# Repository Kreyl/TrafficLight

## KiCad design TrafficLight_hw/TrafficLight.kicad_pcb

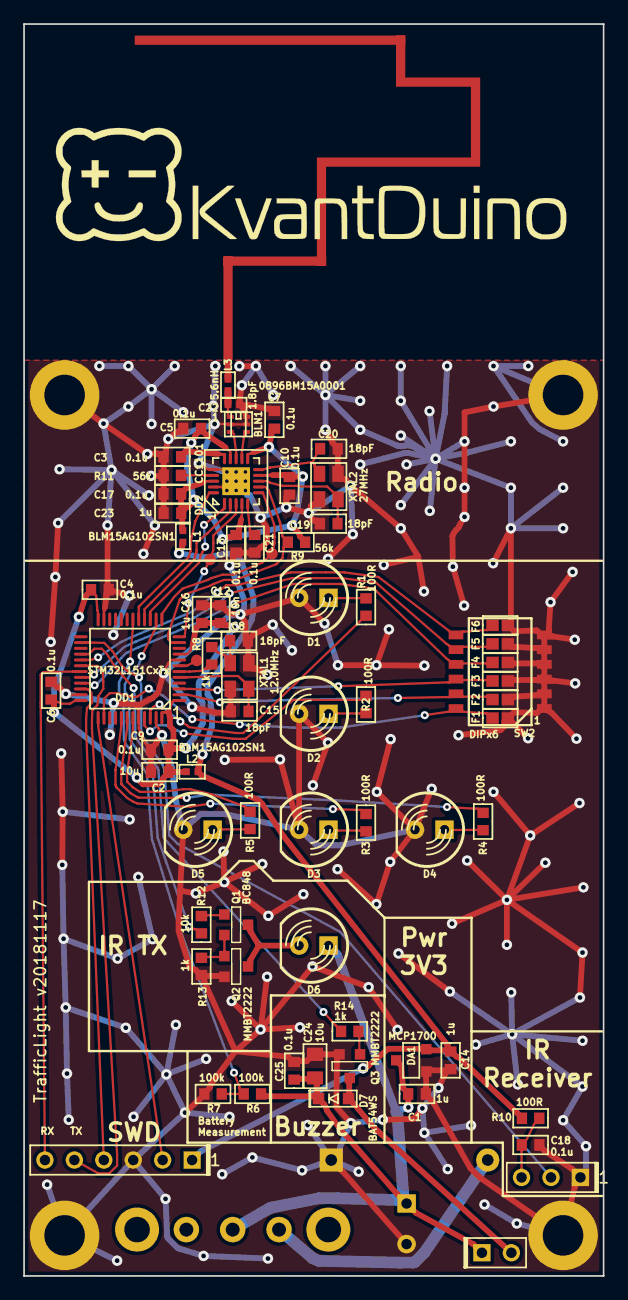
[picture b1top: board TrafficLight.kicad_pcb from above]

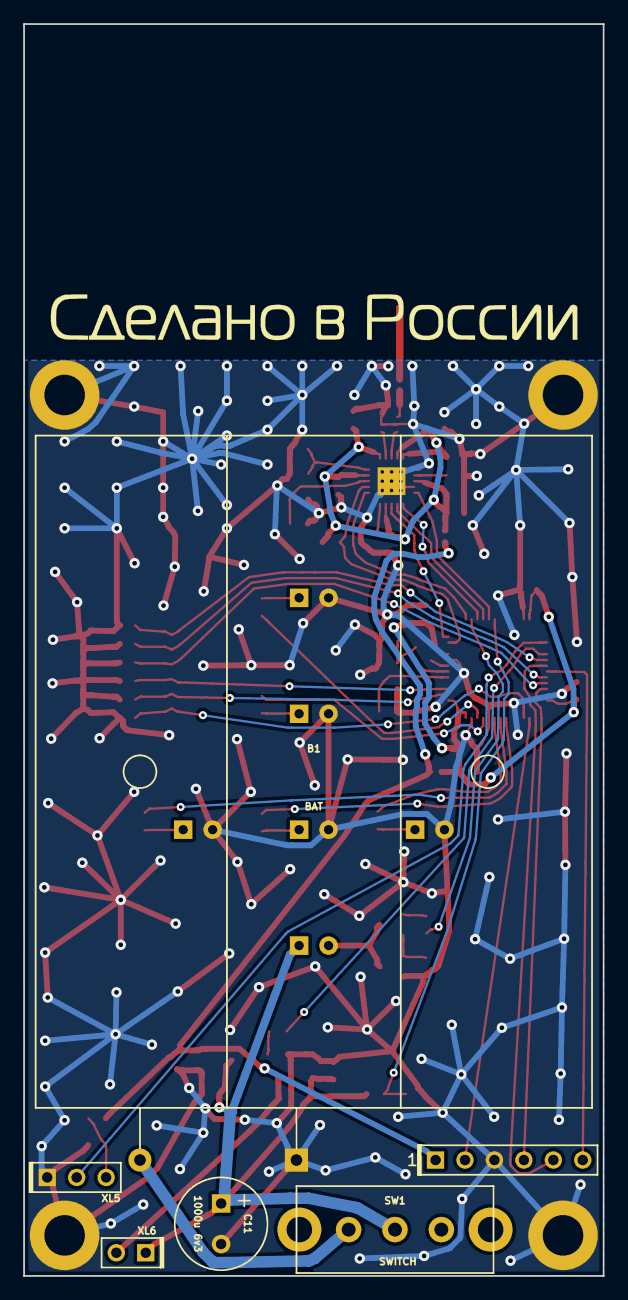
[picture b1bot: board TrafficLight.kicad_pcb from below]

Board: 2 copper layers, 50.0 x 108.0 mm, 80 parts (7 on the bottom side), 54 nets.

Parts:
ANT1: ANT_PCB_MONO; ANT_868_MEANDER_4HOR_35mm
B1: BAT; BAT_HOLDER_3xAA
BLN1: 0896BM15A0001; BALUN_JOHANSON868
C1, C14, C16, C23: 1u; CAP_0603
C2: 10u; CAP_0603
C3, C4, C5, C6, C7, C9, C10, C13, C17, C18, C21, C25: 0.1u; CAP_0603
C8, C15, C19, C20: 18pF; CAP_0603
C11: 1000u 6v3; CAP_08xxR
C12: 10n; CAP_0603
C22: 1.8pF; CAP_0402
C24: 10u; CAP_0805
D1, D2, D3, D4, D5, D6: LED; LED_Through-Hole-5mm
D7: BAT54WS; SOD323
DA1: MCP1700; SOT23-3A
DD1: STM32L151CxTx; LQFP48
DD2: CC1101; QFN20
F1, F2, F3, F4, F5, F6: Fuse0R; RES_0603_FUSE
HOLE1, HOLE2, HOLE3, HOLE4: HOLE_METALLED; Hole3_5_out6mm
L1, L2: BLM15AG102SN1; IND_0402
L3: 5.6nH; IND_0402
Logo1: Logo; KvantduinoLogoText_44d4
Logo3: Logo; MadeInRussia_47d4
Q1: BC848; SOT23-3
Q2, Q3: MMBT2222; SOT23-3
R1, R2, R3, R4, R5, R10: 100R; RES_0603
R6, R7: 100k; RES_0603
R8, R13, R14: 1k; RES_0603
R9, R11: 56k; RES_0603
R12: 10k; RES_0603
SW1: SWITCH; SW_SS9
SW2: DIPx6; DIP_SMD_1D27X6
TP1, TP2, TP3: TESTPOINT; TESTPOINT_1MM
XL1: CONN_6; PLS-6
XL5: CONN_3; PLS-3
XL6: CONN_2; PLS-2
XTAL1: 12.0MHz; 03225C4
XTAL2: 27MHz; 03225C4

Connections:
+3.3V: C14.1, DA1.2, L1.2, L2.2, R10.2, XL1.1
+BATT: C1.1, C11.1, C24.1, C25.1, D6.A, D7.C, DA1.3, R6.1, SW1.2, XL6.1
/ANT1: BLN1.1, C22.1, L3.2
/ANT2: ANT1.1, L3.1
/BAT_IN: B1.A, SW1.1
/BAT_MEAS: DD1.18, R6.2, R7.1
/Buzzer: DD1.28, R14.1
/CC_CS: DD1.11, DD2.7, R9.1
/CC_GDO0: DD1.13, DD2.6, TP2.1
/CC_GDO2: DD1.12, DD2.3, TP3.1
/CC_MISO: DD1.16, DD2.2
/CC_MOSI: DD1.17, DD2.20
/CC_SCK: DD1.15, DD2.1
/DS1: DD1.38, F1.1, SW2.12
/DS2: DD1.2, F2.1, SW2.11
/DS3: DD1.3, F3.1, SW2.10
/DS4: DD1.33, F4.1, SW2.9
/DS5: DD1.32, F5.1, SW2.8
/DS6: DD1.29, F6.1, SW2.7
/IR_LED: DD1.14, R12.1
/IR_LED_OUT: D6.C, Q1.3, Q2.3
/IR_RX: DD1.26, XL5.2
/LEFT_LED: DD1.43, R5.1
/RED_LED: DD1.46, R1.1
/RF1: BLN1.4, DD2.12
/RF2: BLN1.3, DD2.13
/RIGHT_LED: DD1.42, R4.1
/STRAIGHT_LED: DD1.41, R3.1
/SWCLK: DD1.37, XL1.2
/SWDIO: DD1.34, XL1.4
/UART_RX: DD1.31, XL1.6
/UART_TX: DD1.30, XL1.5
/VibroOut: D7.A, Q3.3, XL6.2
/YELLOW_LED: DD1.45, R2.1
GND: B1.C, BLN1.2, BLN1.5, BLN1.6, C1.2, C2.2, C3.2, C4.2, C5.2, C6.2, C7.2, C8.2, C9.2, C10.2, C11.2, C12.2, C13.2, C14.2, C15.2, C16.2, C17.2, C18.1, C19.2, C20.2, C21.2, C22.2, C23.2, C24.2, C25.2, D1.C, D2.C, D3.C, D4.C, D5.C, DA1.1, DD1.8, DD1.23, DD1.35, DD1.44, DD1.47, DD2.16, DD2.19, DD2.PAD, F1.2, F2.2, F3.2, F4.2, F5.2, F6.2, HOLE1.H, HOLE2.H, HOLE3.H, HOLE4.H, Q2.2, Q3.2, R7.2, R11.2, R13.1, SW2.1, SW2.2, SW2.3, SW2.4, SW2.5, SW2.6, XL1.3, XL5.1, XTAL1.H, XTAL2.H
unnamed: C8.1, R8.2, XTAL1.1
unnamed: C15.1, DD1.5, XTAL1.2
unnamed: C18.2, R10.1, XL5.3
unnamed: C19.1, DD2.8, XTAL2.1
unnamed: C20.1, DD2.10, XTAL2.2
unnamed: C21.1, DD2.5
unnamed: D1.A, R1.2
unnamed: D2.A, R2.2
unnamed: D3.A, R3.2
unnamed: D4.A, R4.2
unnamed: D5.A, R5.2
unnamed: DD1.6, R8.1
unnamed: DD1.7, TP1.1
unnamed: DD2.17, R11.1
unnamed: Q1.1, R12.2
unnamed: Q1.2, Q2.1, R13.2
unnamed: Q3.1, R14.2
PwrMCU: C2.1, C4.1, C6.1, C9.1, C12.1, C16.1, DD1.1, DD1.9, DD1.24, DD1.36, DD1.48, L2.1
VCC: C3.1, C5.1, C7.1, C10.1, C13.1, C17.1, C23.1, DD2.4, DD2.9, DD2.11, DD2.14, DD2.15, DD2.18, L1.1, R9.2

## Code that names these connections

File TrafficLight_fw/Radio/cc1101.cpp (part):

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#include "uart.h"

cc1101_t CC;
static const PinIrq_t IGdo0 {CC_GDO0};
static thread_reference_t ThdRef;

#define CsHi()  PinSet(CC_GPIO, CC_CS)
#define CsLo()  PinClear(CC_GPIO, CC_CS)

uint8_t cc1101_t::Init() {
    // ==== GPIO ====
    PinSetupOut      (CC_GPIO, CC_CS,   omPushPull, pudNone);
    PinSetupAlterFunc(CC_GPIO, CC_SCK,  omPushPull, pudNone, CC_SPI_AF);
    PinSetupAlterFunc(CC_GPIO, CC_MISO, omPushPull, pudNone, CC_SPI_AF);
    PinSetupAlterFunc(CC_GPIO, CC_MOSI, omPushPull, pudNone, CC_SPI_AF);
    IGdo0.Init(CC_GPIO, pudNone, ttFalling);
//    PinSetupIn       (CC_GPIO, CC_GDO2, pudNone);
    PinSetupAnalog   (CC_GPIO, CC_GDO2);    // GDO2 not used
    CsHi();
    // ==== SPI ==== 6.5MHz max! MSB first, master, ClkLowIdle, FirstEdge, Baudrate=f/2
    ISpi.Setup(CC_SPI, boMSB, cpolIdleLow, cphaFirstEdge, sbFdiv4);
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
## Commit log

2016-02-28 sch in progress
2016-02-28 Proceeding with PCB
2016-02-28 topor done
2016-02-29 + PCB routing completed
2016-03-05 + FW started, uart works
2016-03-06 Sch: * CC Quartz capacitors 18pF * Antenna
2016-03-06 + DipSwitch
2016-03-06 + Lights controlled + IR
2016-03-23 gitignore
2016-03-23 + Recent kl_lib
2016-03-28 * CC init several tries * Different failure indication * IR TX 20 times per second
2016-04-01 Clean-up
2016-04-24 Minor changes
2016-12-18 * Switch to newer libs * ID stored in EEPROM
2018-12-02 + Quantduino PCB
2018-12-02 Switch to Atollic. Does not work.
2018-12-02 Seems working
2019-02-01 Smth
